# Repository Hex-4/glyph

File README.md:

# [ GLYPH_ ]
[ a custom split keyboard ]

[ for portably and comfortably interfacing with computing systems ]

Glyph is the keyboard I wish I had. It's a finger-staggered split mechanical keyboard with hotswap support, powered by the Raspberry Pi Pico and ~~KMK~~ QMK firmware. The main gimmick is a joystick next to each thumb switch that acts as a novel way to switch layers, run macros, and navigate documents.

I had made the Hexapad (a macropad) before, but I wanted something to replace my Keychron. It was a pretty nice board, but it had a boring standard layout, non-customizable firmware, and no extra features apart from a per-key white backlight. I saw a video on youtube about someone making their own custom split keyboard, and that planted the seed in my head. When Highway was announced I was sure that this would be my first project. Glyph has a 6x3 main grid on each side, and instead of a vanilla thumb cluster, it has one thumb button and a joystick.

[{ visit the journal }](JOURNAL.md)

[{ demo video }](https://www.youtube.com/watch?v=N5a5DT0hNs8)

[{ left pcb }](https://kicanvas.org/?github=https://github.com/Hex-4/glyph/tree/main/PCB/left)

[{ right pcb }](https://kicanvas.org/?github=https://github.com/Hex-4/glyph/tree/main/PCB/right)

[{ case }](https://cad.onshape.com/documents/a309a43e7ab9d98fd3e56af4/w/ec765f4ff1bc21db4a251eb8/e/62d9ee1d9fa6e5db3ba2bbb2?renderMode=0&uiState=685db91bc2e0c400d63d1642)

[ made with [Hack Club's](https://hack.club) [Highway](https://highway.hackclub.com/?ref=recNHETbc0csFrnMW), a hardware grant program for teen hackers ]

## [ BOM ]

| prices in CAD | ITEM                                | INFO                                                                     | COST PER ONE | QUANTITY                         | TOTAL COST | SOURCE                                                                                                                  |   |   |   |
|---------------|-------------------------------------|--------------------------------------------------------------------------|--------------|----------------------------------|------------|-------------------------------------------------------------------------------------------------------------------------|---|---|---|
| COMPONENTS    | MX switches                         | It's a keyboard                                                          | ~$0\.29      | 38                               | ~$12       | Already own                                                                                                             |   |   |   |
|               | Hotswap sockets                     | To swap out switches if needed                                           | $0\.15       | 40 \(comes in packs of 20\)      | $10\.68    | https://www\.aliexpress\.com/item/1005008954571807\.html?mp=1                                                           |   |   |   |
|               | Raspberry Pi Pico \(or equivalent\) | So that the fifteen minutes I spent writing firmware doesn't go to waste | ~$4          | 2                                | ~$8        | Already own                                                                                                             |   |   |   |
|               | COM\-09032 joystick                 | \[glyph\]'s gimmick                                                      | ~$8          | 2                                | ~$16       | Already own                                                                                                             |   |   |   |
|               | Diodes                              | The Matrix                                                               | $0\.04       | 36 \(thumbs are directly wired\) | $3\.91     | https://www\.aliexpress\.com/item/1005007131309837\.html?mp=1                                                           |   |   |   |
|               | TRRS jack                           | for communication with the other side                                    | $0\.29       | 10 \(will use 2\)                | $2\.89     | https://www\.aliexpress\.com/item/33029465106\.html?mp=1                                                                |   |   |   |
|               | Capacitors                          | for RGB                                                                  | $0\.39       | 10 \(will use 6\)                | $3\.93     | https://www.aliexpress.com/item/1005009302222368.html?mp=1 |   |   |   |
|               | RGB LEDs                            | glowy :3                                                                 | $0\.16       | 20 \(will use 12\)               | $3\.15     | https://www\.aliexpress\.com/item/1005005193716172\.html                                                                |   |   |   |
|               | Components total                    |                                                                          |              |                                  | $23\.96    | AliExpress                                                                                                              |   |   |   |
|               |                                     |                                                                          |              |                                  |            |                                                                                                                         |   |   |   |
| PCB           | Left\-side PCB                      | Handwiring is hard                                                       | $12\.59      | 1                                | $12\.59    | JLCPCB                                                                                                                  |   |   |   |
|               | Right\-side PCB                     |                                                                          | $12\.87      | 1                                | $12\.87    | JLCPCB                                                                                                                  |   |   |   |
|               | Estimated shipping                  | Cheapest option                                                          | $14\.84      | 1                                | $14\.84    | JLCPCB                                                                                                                  |   |   |   |
|               | PCB total                           |                                                                          |              |                                  | $40\.30    |                                                                                                                         |   |   |   |
|               |                                     |                                                                          |              |                                  |            |                                                                                                                         |   |   |   |
| MISC          | M4 nuts and bolts                   |                                                                          | ~$0\.50      | 16                               | ~$8        | Already own                                                                                                             |   |   |   |
|               | Keycaps                             | MOA profile for my nonstandard layout                                    | $22\.99      | 1                                | $22\.99    | https://www\.aliexpress\.com/item/1005009118477177\.html                                                                |   |   |   |
|               |                                     |                                                                          |              |                                  |            |                                                                                                                         |   |   |   |
| TOTAL         | Parts already bought                |                                                                          |              |                                  | ~$44       |                                                                                                                         |   |   |   |
|               | Subtotal                            |                                                                          |              |                                  | $87\.25    |                                                                                                                         |   |   |   |
|               | With tax \(5% GST\)                 |                                                                          |              |                                  | $91\.61    |                                                                                                                         |   |   |   |
|               | With tax \+ buffer                  | in case of e\.g extra taxes                                              | etc          |                                  | $100       |                                                                                                                         |   |   |   |

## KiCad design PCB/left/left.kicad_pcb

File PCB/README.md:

# [ GLYPH :: PCB ]

This folder stores Glyph's PCB and its libraries. Thanks to the [scotto-kicad](https://github.com/joe-scotto/scottokeebs/tree/main/Extras/ScottoKicad) KiCad footprint and symbol library and SnapMagic for not having an up-to-date KiCad plugin and making me manually download the joystick footprint.

There are two KiCad projects, one for each side. I've tried my best to make sure they use relative paths, but please let me know if something fails to open for you.

[ view online via kicanvas: ]

(you may need to hide the edge.cuts layer)

[{ left }](https://kicanvas.org/?github=https://github.com/Hex-4/glyph/tree/main/PCB/left)

[{ right }](https://kicanvas.org/?github=https://github.com/Hex-4/glyph/tree/main/PCB/right)

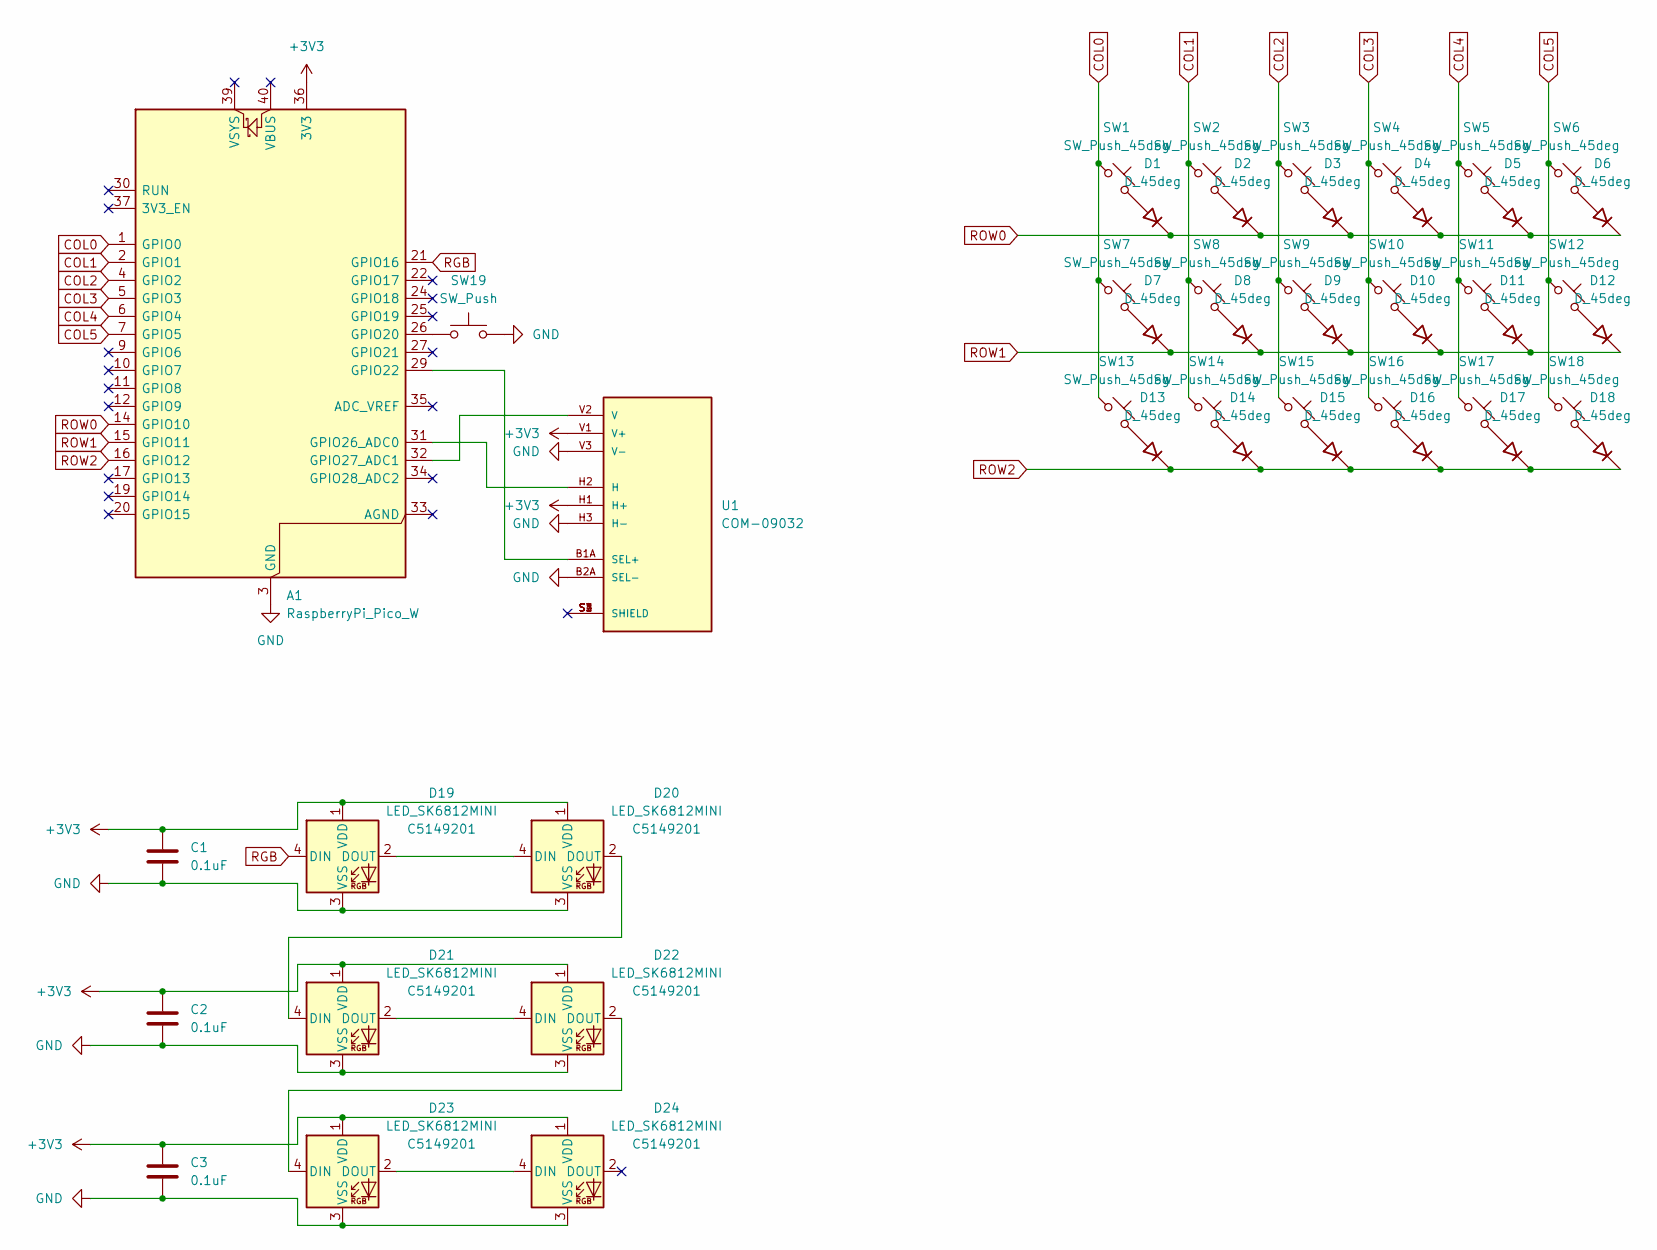
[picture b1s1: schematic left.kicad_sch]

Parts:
A1: RaspberryPi_Pico_W; RaspberryPi_Pico_Common_THT
C1, C2, C3: 0.1uF; C_Disc_D3.0mm_W1.6mm_P2.50mm
D1, D2, D3, D4, D5, D6, D7, D8, D9, D10, D11, D12, D13, D14, D15, D16, D17, D18: D_45deg; D_DO-35_SOD27_P7.62mm_Horizontal
D19, D20, D21, D22, D23, D24: LED_SK6812MINI; LCSC C5149201
SW1, SW2, SW3, SW4, SW5, SW6, SW7, SW8, SW9, SW10, SW11, SW12, SW13, SW14, SW15, SW16, SW17, SW18: SW_Push_45deg; Hotswap_MX_Plated
SW19: SW_Push; Hotswap_MX_Plated
U1: COM-09032; XDCR_COM-09032; PARTREV N/A

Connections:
+3V3: A1.36 (3V3), C1.1, C2.1, C3.1, D19.1 (VDD), D20.1 (VDD), D21.1 (VDD), D22.1 (VDD), D23.1 (VDD), D24.1 (VDD), U1.H1 (H+), U1.V1 (V+)
COL0: A1.1 (GPIO0), SW1.1, SW7.1, SW13.1
COL1: A1.2 (GPIO1), SW2.1, SW8.1, SW14.1
COL2: A1.4 (GPIO2), SW3.1, SW9.1, SW15.1
COL3: A1.5 (GPIO3), SW4.1, SW10.1, SW16.1
COL4: A1.6 (GPIO4), SW5.1, SW11.1, SW17.1
COL5: A1.7 (GPIO5), SW6.1, SW12.1, SW18.1
GND: A1.3 (GND), A1.8 (GND), A1.13 (GND), A1.18 (GND), A1.23 (GND), A1.28 (GND), A1.38 (GND), C1.2, C2.2, C3.2, D19.3 (VSS), D20.3 (VSS), D21.3 (VSS), D22.3 (VSS), D23.3 (VSS), D24.3 (VSS), SW19.2, U1.B2A (SEL-), U1.H3 (H-), U1.V3 (V-); also elsewhere on the board
unnamed: A1.26 (GPIO20), SW19.1
unnamed: A1.29 (GPIO22), U1.B1A (SEL+)
unnamed: A1.31 (GPIO26_ADC0), U1.H2 (H)
unnamed: A1.32 (GPIO27_ADC1), U1.V2 (V)
unnamed 12: A1.40 (VBUS); also elsewhere on the board
unnamed: D1.2 (A), SW1.2
unnamed: D2.2 (A), SW2.2
unnamed: D3.2 (A), SW3.2
unnamed: D4.2 (A), SW4.2
unnamed: D5.2 (A), SW5.2
unnamed: D6.2 (A), SW6.2
unnamed: D7.2 (A), SW7.2
unnamed: D8.2 (A), SW8.2
unnamed: D9.2 (A), SW9.2
unnamed: D10.2 (A), SW10.2
unnamed: D11.2 (A), SW11.2
unnamed: D12.2 (A), SW12.2
unnamed: D13.2 (A), SW13.2
unnamed: D14.2 (A), SW14.2
unnamed: D15.2 (A), SW15.2
unnamed: D16.2 (A), SW16.2
unnamed: D17.2 (A), SW17.2
unnamed: D18.2 (A), SW18.2
unnamed: D19.2 (DOUT), D20.4 (DIN)
unnamed: D20.2 (DOUT), D21.4 (DIN)
unnamed: D21.2 (DOUT), D22.4 (DIN)
unnamed: D22.2 (DOUT), D23.4 (DIN)
unnamed: D23.2 (DOUT), D24.4 (DIN)
RGB: A1.21 (GPIO16), D19.4 (DIN)
ROW0: A1.14 (GPIO10), D1.1 (K), D2.1 (K), D3.1 (K), D4.1 (K), D5.1 (K), D6.1 (K)
ROW1: A1.15 (GPIO11), D7.1 (K), D8.1 (K), D9.1 (K), D10.1 (K), D11.1 (K), D12.1 (K)
ROW2: A1.16 (GPIO12), D13.1 (K), D14.1 (K), D15.1 (K), D16.1 (K), D17.1 (K), D18.1 (K)
RX: A1.12 (GPIO9); also elsewhere on the board
TX: A1.11 (GPIO8); also elsewhere on the board

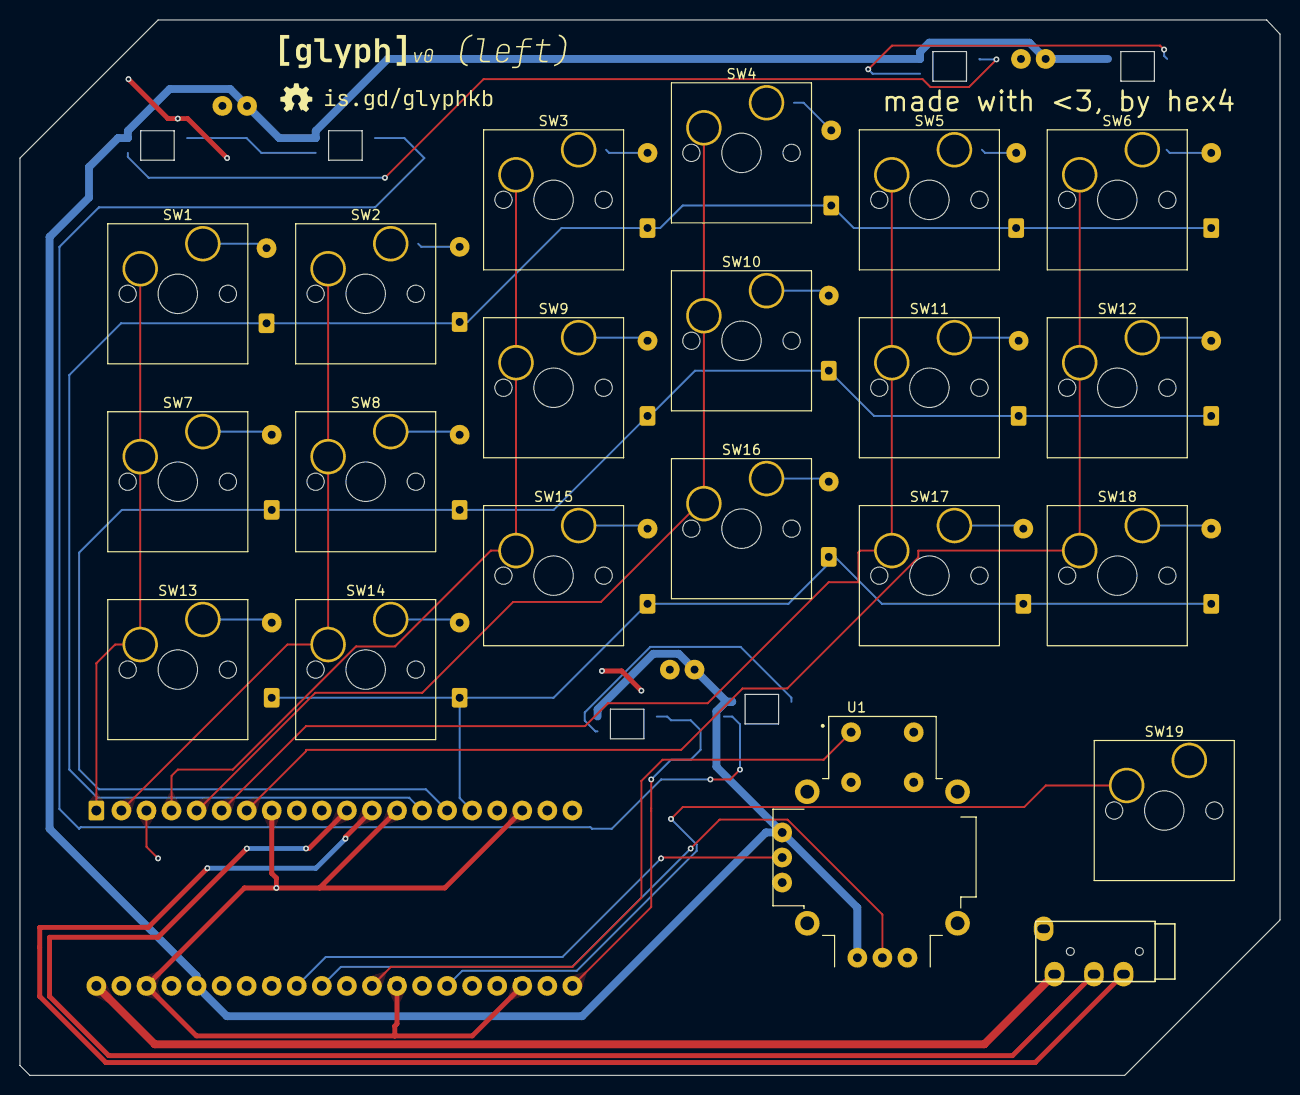
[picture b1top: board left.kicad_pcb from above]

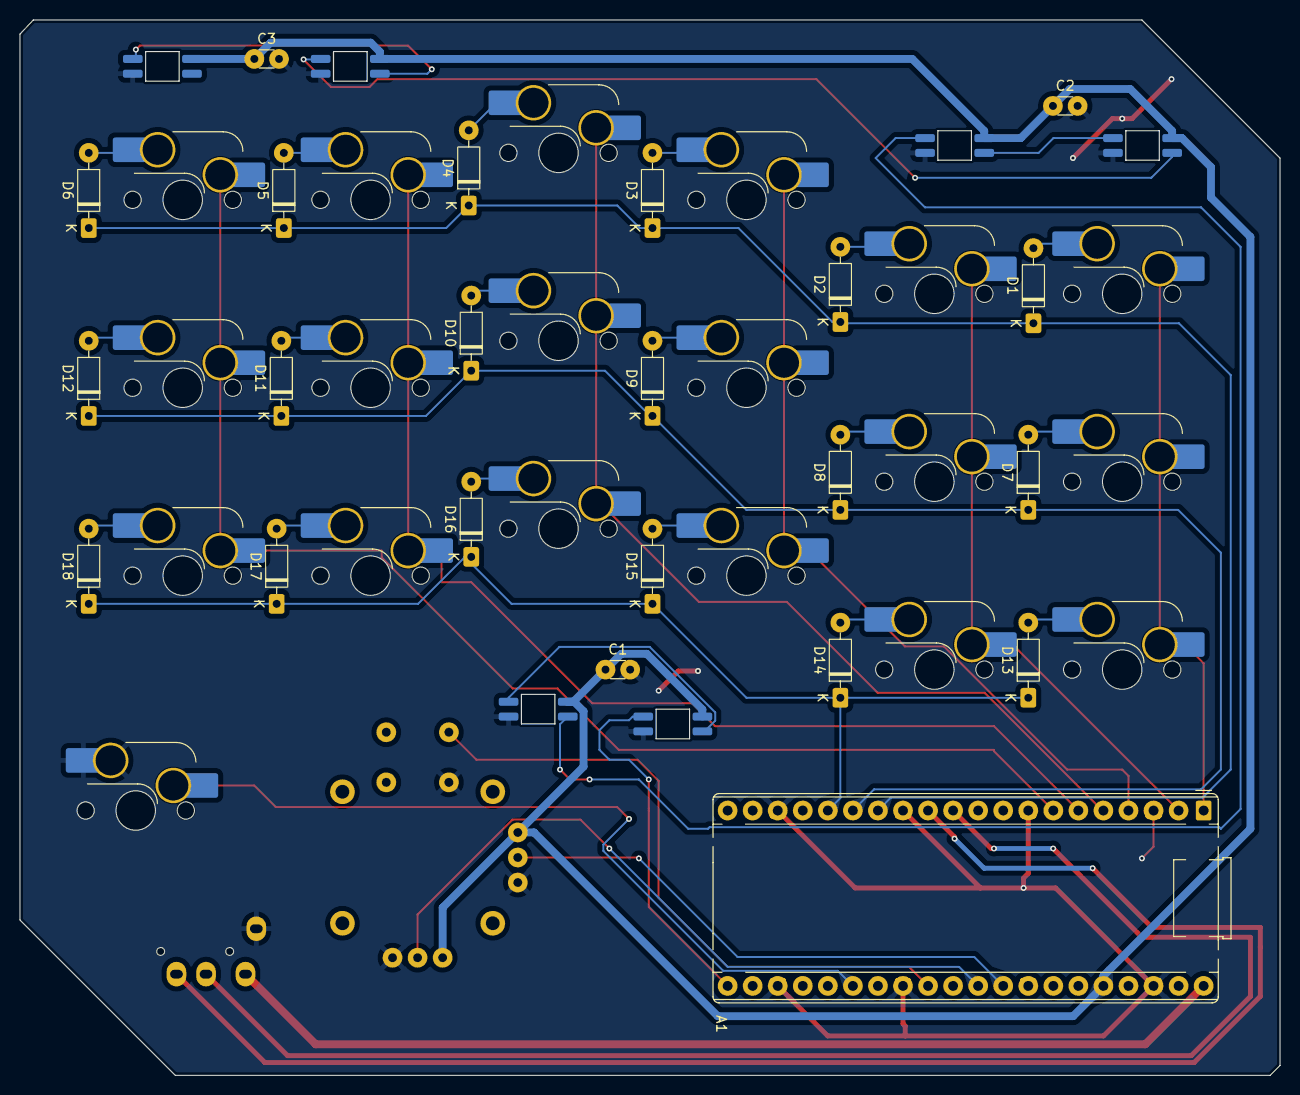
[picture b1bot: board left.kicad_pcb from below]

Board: 2 copper layers, 127.7 x 106.9 mm, 49 parts (28 on the bottom side), 42 nets.

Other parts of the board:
U2: TRRS; TRRS_PJ-320A

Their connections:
GND: U2.1 (SLEEVE); also elsewhere on the board
unnamed 12: U2.2 (TIP); also elsewhere on the board
RX: U2.4 (RING2); also elsewhere on the board
TX: U2.3 (RING1); also elsewhere on the board

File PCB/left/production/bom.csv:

Designator,Footprint,Quantity,Value,LCSC Part #
A1,RaspberryPi_Pico_Common_THT,1,RaspberryPi_Pico_W,
"C1, C2, C3",C_Disc_D3.0mm_W1.6mm_P2.50mm,3,0.1uF,
"D1, D10, D11, D12, D13, D14, D15, D16, D17, D18, D2, D3, D4, D5, D6, D7, D8, D9",D_DO-35_SOD27_P7.62mm_Horizontal-bigpads,18,D_45deg,
"D19, D20, D21, D22, D23, D24",LED_SK6812MINI,6,LED_SK6812MINI,C5149201
"SW1, SW10, SW11, SW12, SW13, SW14, SW15, SW16, SW17, SW18, SW2, SW3, SW4, SW5, SW6, SW7, SW8, SW9",Hotswap_MX_Plated,18,SW_Push_45deg,
SW19,Hotswap_MX_Plated,1,SW_Push,
U1,XDCR_COM-09032,1,COM-09032,
U2,TRRS_PJ-320A,1,TRRS,

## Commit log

2025-05-27 May 27: Layout
2025-05-30 wrong image
2025-05-30 [ MAY 29 // BASICS ]
2025-05-31 [ MAY 29 // BASICS :: FILES ]
2025-06-02 [ MAY 31 // GLOW ]
2025-06-02 [ MAY 31 // GLOW :: JOURNAL ]
2025-06-05 [ JUN 4 // ARRANGEMENTS ]
2025-06-05 [ JUN 4 // ARRANGEMENTS :: JOURNAL ]
2025-06-09 [ JUN 9 // ROUTING :: JOURNAL ]
2025-06-09 [ JUN 9 // ROUTING ]
2025-06-15 [ JUN 14 // REPLICATION ]
2025-06-15 [ JUN 14 // REPLICATION :: JOURNAL ]
2025-06-21 [ JUN 20 // MICRO :: JOURNAL ]
2025-06-21 [ JUN 20 // MICRO ]
2025-06-22 [ JUN 21 // MODEL :: JOURNAL ]
2025-06-22 [ JUN 21 // MODEL ]
2025-06-22 [ JUN 22 // ALMOST :: JOURNAL ]
2025-06-26 [ JUN 25 // FINALITY (?) :: JOURNAL]
2025-06-26 [ JUN 25 // FINALITY (?) ]
2025-06-27 [ JUN 26 // SUBMISSION ]
2025-06-27 ( add bom )
2025-06-27 ( fix bom in readme )
2025-06-29 ( bom update )
2025-06-29 ( update bom in readme )
2025-06-30 ( i need to go to sleep )
2025-07-03 ( finish journal )
2025-07-25 [ JUL 24 // SOLDER ]
2025-07-26 [ JUL 25 // PROBLEMS :: JOURNAL ]
2025-07-26 [ JUL 25 // PROBLEMS ]
2025-08-07 [ JUL 29 // REALITY ]
2025-08-08 [ AUG 7 // OOPS ]
2025-08-12 [ AUG 11 // HOPE ]
2025-08-13 [ AUG 12 // QUANTUM ]
2025-08-14 [ AUG 13 // DONE ]
2025-08-14 ( add demo video )
2025-08-14 [ AUG 13 // COMPLETION :: JOURNAL ]
